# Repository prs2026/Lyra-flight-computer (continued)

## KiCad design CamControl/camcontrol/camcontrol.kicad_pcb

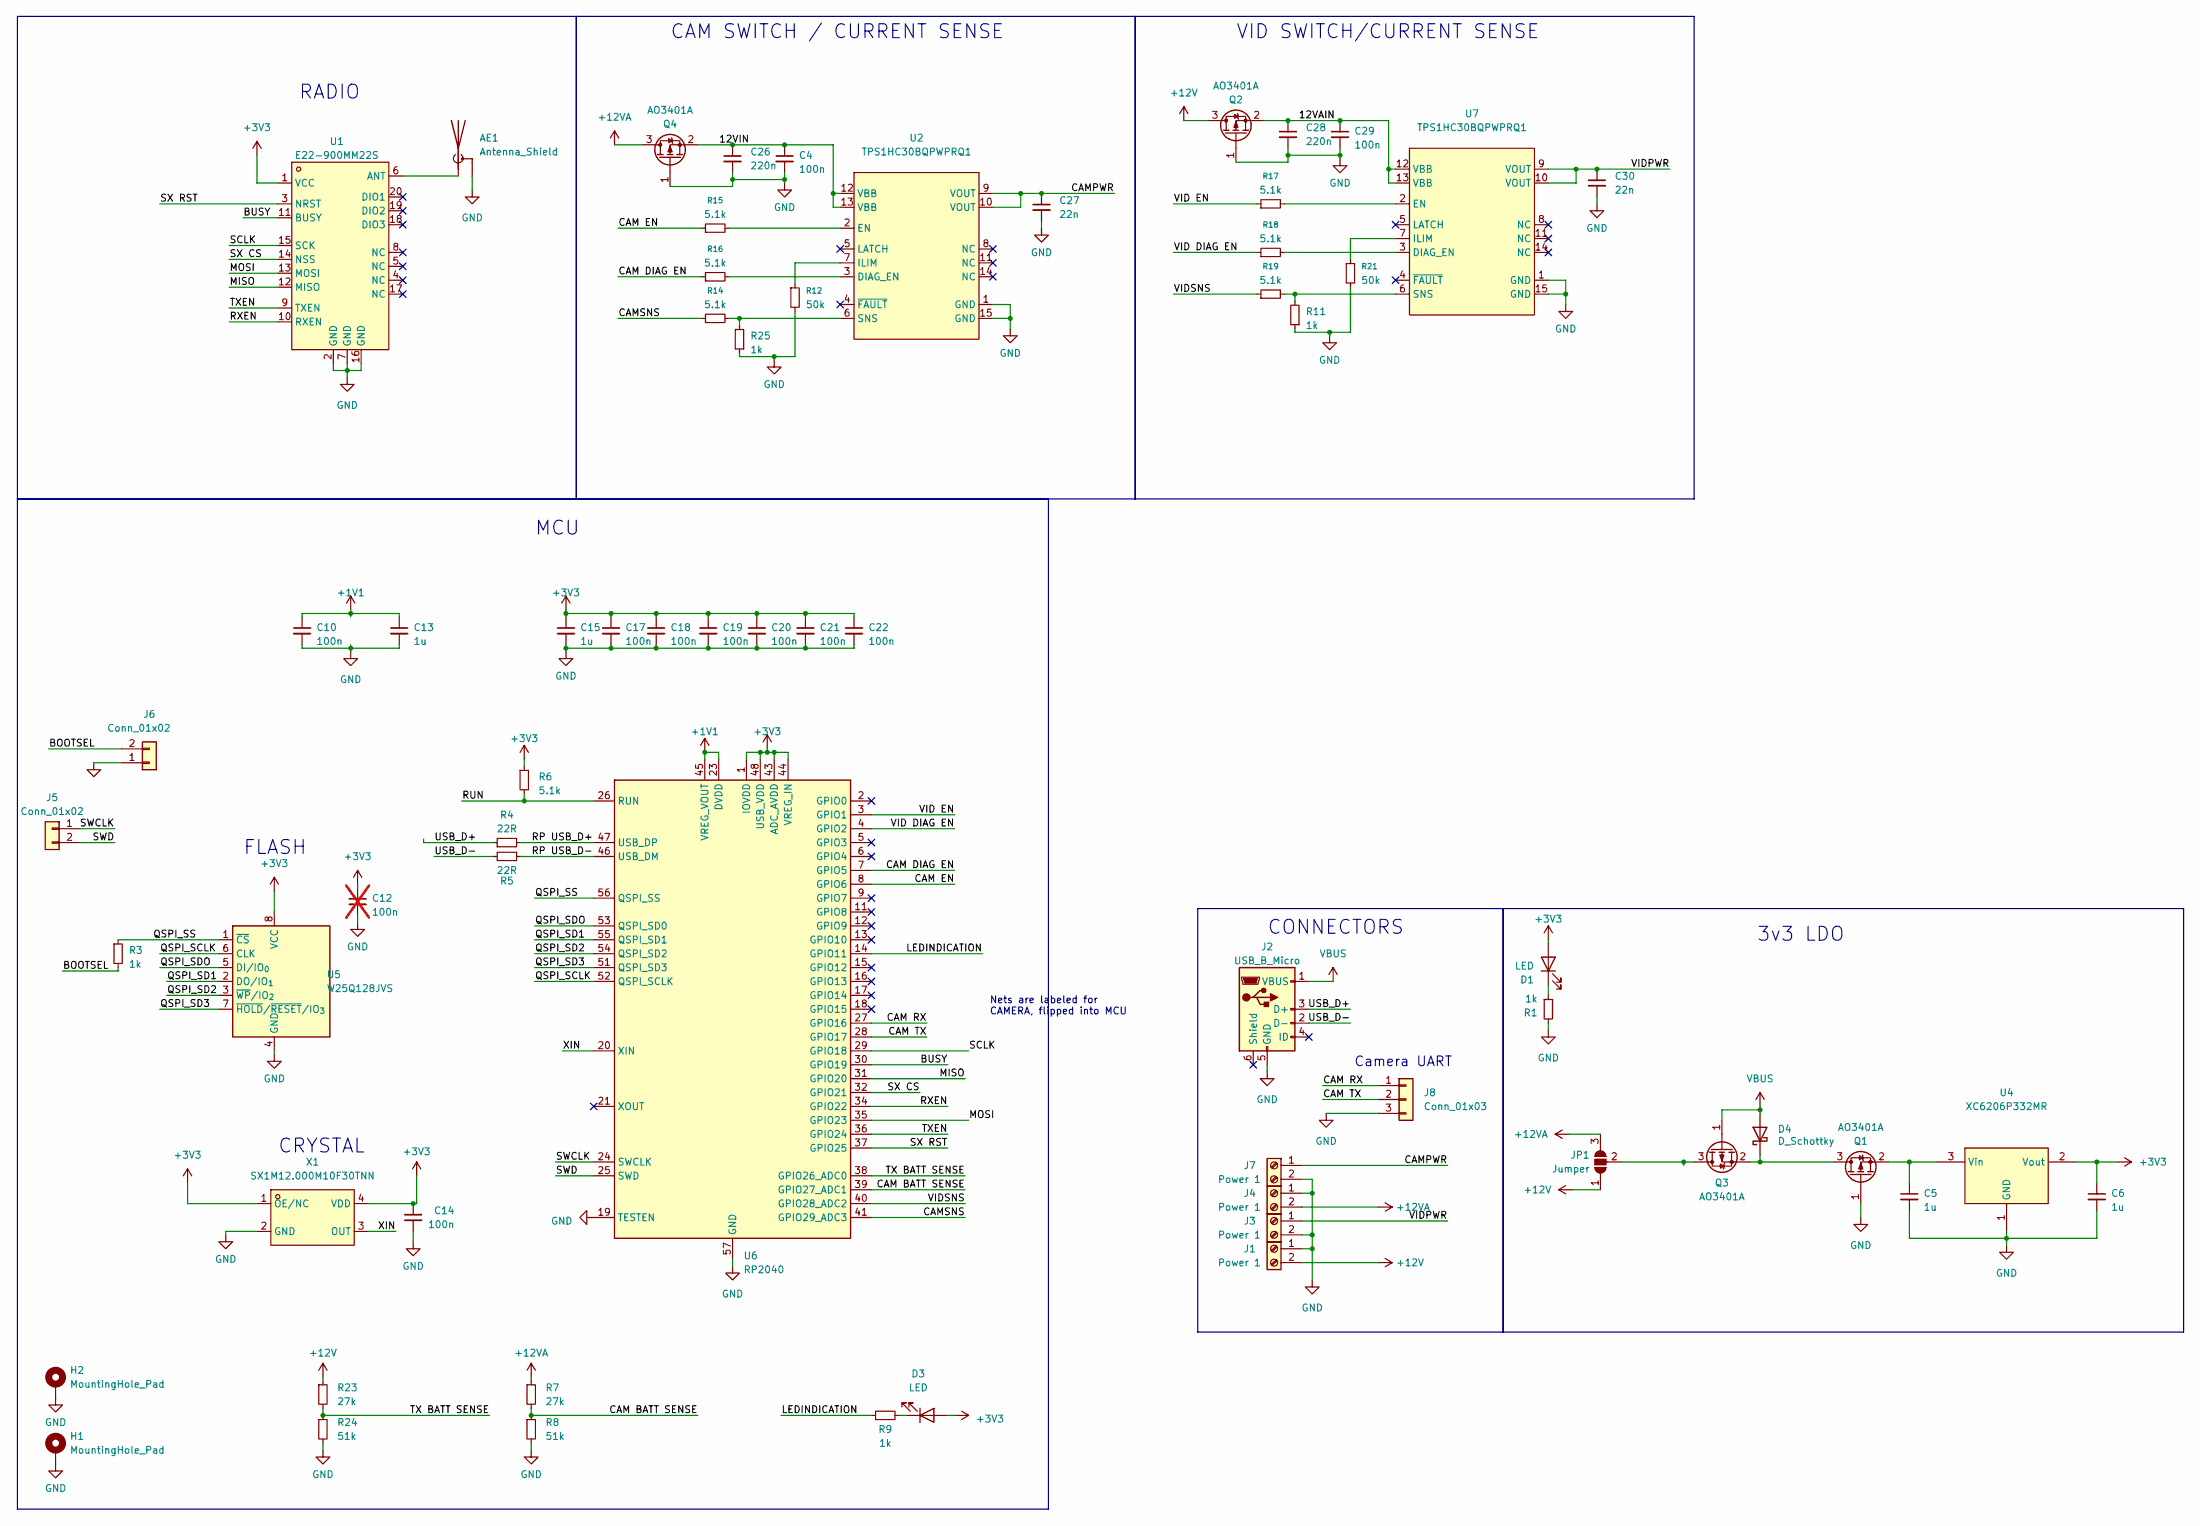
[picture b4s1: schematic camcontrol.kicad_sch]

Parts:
AE1: Antenna_Shield; ANT-SMD_1909763-1; LCSC Part C392444
C4, C10, C14, C17, C18, C19, C20, C21, C22, C29: 100n; C_0402_1005Metric; LCSC Part C1525
C5, C6, C13, C15: 1u; C_0402_1005Metric; LCSC Part C52923
C12: 100n; C_0402_1005Metric; LCSC Part C1525; not fitted
C26, C28: 220n; C_0402_1005Metric; LCSC Part C16772
C27, C30: 22n; C_0402_1005Metric; LCSC Part C1532
D1, D3: LED; LED_0603_1608Metric; LCSC Part C89811
D4: D_Schottky; D_SOD-323F; LCSC Part C191023
H1, H2: MountingHole_Pad; MountingHole_2.2mm_M2_DIN965_Pad
J1, J3, J4, J7: Power 1; wago2pin3mmspace
J2: USB_B_Micro; MICRO-USB-SMD_U254-051T-4BHJ25-F2S; LCSC Part C381143
J5: Conn_01x02; SolderJumper-2_P1.3mm_Open_Pad1.0x1.5mm
J6: Conn_01x02; SolderJumper-2_P1.3mm_Open_RoundedPad1.0x1.5mm
J8: Conn_01x03; PinHeader_1x03_P2.00mm_Vertical
JP1: Jumper; SolderJumper-3_P1.3mm_Open_RoundedPad1.0x1.5mm
Q1, Q2, Q3, Q4: AO3401A; SOT-23; LCSC Part C15127
R1, R3, R9, R11, R25: 1k; R_0402_1005Metric; LCSC Part C11702
R4, R5: 22R; R_0402_1005Metric; LCSC Part C25092
R6, R14, R15, R16, R17, R18, R19: 5.1k; R_0402_1005Metric; LCSC Part C25905
R7, R23: 27k; R_0402_1005Metric; LCSC Part C25771
R8, R24: 51k; R_0402_1005Metric; LCSC Part C25794
R12, R21: 50k; R_0402_1005Metric; LCSC Part C25897
U1: E22-900MM22S; WIRELM-SMD_E22-400MM22S; LCSC Part C5333984
U2, U7: TPS1HC30BQPWPRQ1; HTSSOP-14_L5.0-W4.4-P0.65-LS6.4-BL-EP-3; LCSC Part C7496534
U4: XC6206P332MR; SOT-23-3; LCSC Part C5446
U5: W25Q128JVS; SOIC-8_5.3x5.3mm_P1.27mm; LCSC Part C97521
U6: RP2040; QFN-56-1EP_7x7mm_P0.4mm_EP3.2x3.2mm; LCSC Part C2040
X1: SX1M12.000M10F30TNN; OSC-SMD_4P-L2.0-W1.6-BL; LCSC Part C2901608

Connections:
+1V1: C10.1, C13.1, U6.23 (DVDD), U6.45 (VREG_VOUT), U6.50 (DVDD)
+3V3: C6.1, C12.1, C14.1, C15.1, C17.1, C18.1, C19.1, C20.1, C21.1, C22.1, D1.2 (A), D3.2 (A), R6.1, U1.1 (VCC), U4.2 (Vout), U5.8 (VCC), U6.1 (IOVDD), U6.10 (IOVDD), U6.22 (IOVDD), U6.33 (IOVDD), U6.42 (IOVDD), U6.43 (ADC_AVDD), U6.44 (VREG_IN), U6.48 (USB_VDD), U6.49 (IOVDD), X1.1 (OE/NC), X1.4 (VDD)
+12V: J1.2, JP1.1 (A), Q2.3 (D), R23.1
+12VA: J4.2, JP1.3 (B), Q4.3 (D), R7.1
/12VAIN: C28.1, C29.1, Q2.2 (S), U7.12 (VBB), U7.13 (VBB)
/12VIN: C4.1, C26.1, Q4.2 (S), U2.12 (VBB), U2.13 (VBB)
/BOOTSEL: J6.2, R3.2
/BUSY: U1.11 (BUSY), U6.30 (GPIO19)
/CAM BATT SENSE: R7.2, R8.1, U6.39 (GPIO27_ADC1)
/CAM DIAG EN: R16.1, U6.7 (GPIO5)
/CAM EN: R15.1, U6.8 (GPIO6)
/CAM RX: J8.1, U6.27 (GPIO16)
/CAM TX: J8.2, U6.28 (GPIO17)
/CAMPWR: C27.1, J7.1, U2.9 (VOUT), U2.10 (VOUT)
/CAMSNS: R14.1, U6.41 (GPIO29_ADC3)
/LEDINDICATION: R9.1, U6.14 (GPIO11)
/MISO: U1.12 (MISO), U6.31 (GPIO20)
/MOSI: U1.13 (MOSI), U6.35 (GPIO23)
/QSPI_SCLK: U5.6 (CLK), U6.52 (QSPI_SCLK)
/QSPI_SD1: U5.2 (DO/IO_{1}), U6.55 (QSPI_SD1)
/QSPI_SD2: U5.3 (~WP/IO_{2}), U6.54 (QSPI_SD2)
/QSPI_SD3: U5.7 (~HOLD/~RESET/IO_{3}), U6.51 (QSPI_SD3)
/QSPI_SDO: U5.5 (DI/IO_{0}), U6.53 (QSPI_SD0)
/QSPI_SS: R3.1, U5.1 (~CS), U6.56 (QSPI_SS)
/RP USB_D+: R4.2, U6.47 (USB_DP)
/RP USB_D-: R5.1, U6.46 (USB_DM)
/RUN: R6.2, U6.26 (RUN)
/RXEN: U1.10 (RXEN), U6.34 (GPIO22)
/SCLK: U1.15 (SCK), U6.29 (GPIO18)
/SWCLK: J5.1, U6.24 (SWCLK)
/SWD: J5.2, U6.25 (SWD)
/SX CS: U1.14 (NSS), U6.32 (GPIO21)
/SX RST: U1.3 (NRST), U6.37 (GPIO25)
/TX BATT SENSE: R23.2, R24.1, U6.38 (GPIO26_ADC0)
/TXEN: U1.9 (TXEN), U6.36 (GPIO24)
/USB_D+: J2.3 (D+), R4.1
/USB_D-: J2.2 (D-), R5.2
/VID DIAG EN: R18.1, U6.4 (GPIO2)
/VID EN: R17.1, U6.3 (GPIO1)
/VIDPWR: C30.1, J3.1, U7.9 (VOUT), U7.10 (VOUT)
/VIDSNS: R19.1, U6.40 (GPIO28_ADC2)
/XIN: U6.20 (XIN), X1.3 (OUT)
GND: AE1.2 (Shield), C4.2, C5.2, C6.2, C10.2, C12.2, C13.2, C14.2, C15.2, C17.2, C18.2, C19.2, C20.2, C21.2, C22.2, C26.2, C27.2, C28.2, C29.2, C30.2, H1.1, H2.1, J1.1, J2.5 (GND), J3.2, J4.1, J6.1, J7.2, J8.3, Q1.1 (G), Q2.1 (G), Q4.1 (G), R1.2, R8.2, R11.1, R12.2, R21.2, R24.2, R25.1, U1.2 (GND), U1.7 (GND), U1.16 (GND), U2.1 (GND), U2.15 (GND), U4.1 (GND), U5.4 (GND), U6.19 (TESTEN), U6.57 (GND), U7.1 (GND), U7.15 (GND), X1.2 (GND)
unnamed: AE1.1 (A), U1.6 (ANT)
unnamed: D1.1 (K), R1.1
unnamed: D3.1 (K), R9.2
unnamed: D4.1 (K), Q1.3 (D), Q3.2 (S)
unnamed: JP1.2 (C), Q3.3 (D)
unnamed: C5.1, Q1.2 (S), U4.3 (Vin)
unnamed: R16.2, U2.3 (DIAG_EN)
unnamed: R15.2, U2.2 (EN)
unnamed: R12.1, U2.7 (ILIM)
unnamed: R14.2, R25.2, U2.6 (SNS)
unnamed: R18.2, U7.3 (DIAG_EN)
unnamed: R17.2, U7.2 (EN)
unnamed: R21.1, U7.7 (ILIM)
unnamed: R11.2, R19.2, U7.6 (SNS)
VBUS: D4.2 (A), J2.1 (VBUS), Q3.1 (G)

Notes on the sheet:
CONNECTORS
RADIO
FLASH
Camera UART
MCU
Nets are labeled for CAMERA, flipped into MCU
VID SWITCH/CURRENT SENSE
CAM SWITCH / CURRENT SENSE
3v3 LDO
CRYSTAL

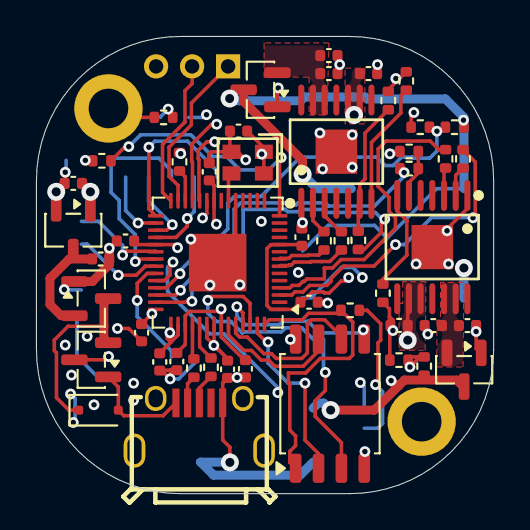
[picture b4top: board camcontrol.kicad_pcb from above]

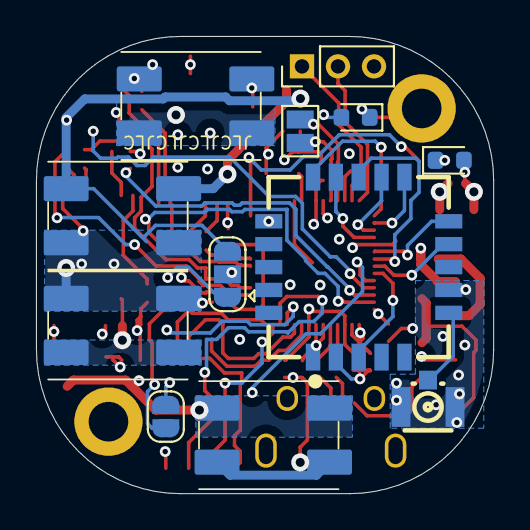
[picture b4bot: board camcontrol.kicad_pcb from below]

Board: 4 copper layers, 25.4 x 25.4 mm, 64 parts (12 on the bottom side), 58 nets.

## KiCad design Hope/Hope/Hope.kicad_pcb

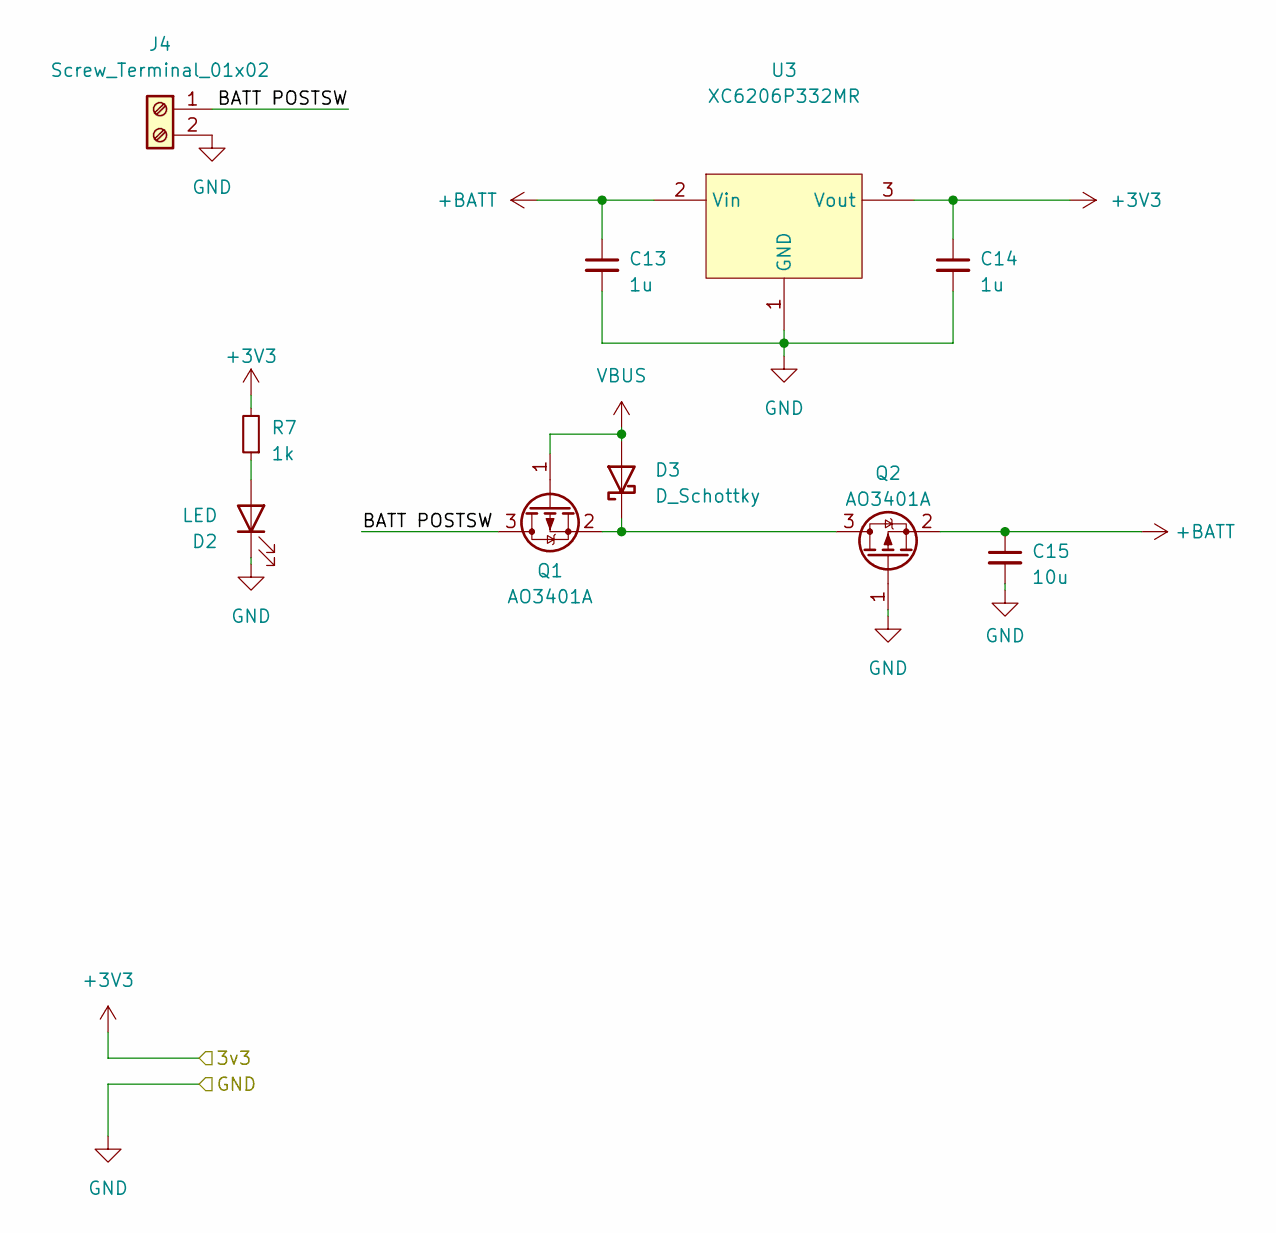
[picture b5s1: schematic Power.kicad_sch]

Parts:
C13, C14: 1u; C_0402_1005Metric; LCSC Part C52923
C15: 10u; C_0603_1608Metric; LCSC Part C96446
D2: LED; LED_0805_2012Metric
D3: D_Schottky; D_SOD-323F; LCSC Part C191023
J4: Screw_Terminal_01x02; TerminalBlock_Phoenix_MPT-0,5-2-2.54_1x02_P2.54mm_Horizontal
Q1, Q2: AO3401A; SOT-23; LCSC Part C15127
R7: 1k; R_0402_1005Metric; LCSC Part C11702
U3: XC6206P332MR; SOT-23-3_L2.9-W1.6-P1.90-LS2.8-BR; LCSC Part C5446

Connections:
+3V3: C14.1, R7.2, U3.3 (Vout); also elsewhere on the board
+BATT: C13.1, C15.1, Q2.2 (S), U3.2 (Vin); also elsewhere on the board
/Power/BATT POSTSW: J4.1, Q1.3 (D)
GND: C13.2, C14.2, C15.2, D2.1 (K), J4.2, Q2.1 (G), U3.1 (GND); also elsewhere on the board
unnamed: D2.2 (A), R7.1
unnamed: D3.1 (K), Q1.2 (S), Q2.3 (D)
VBUS: D3.2 (A), Q1.1 (G); also elsewhere on the board

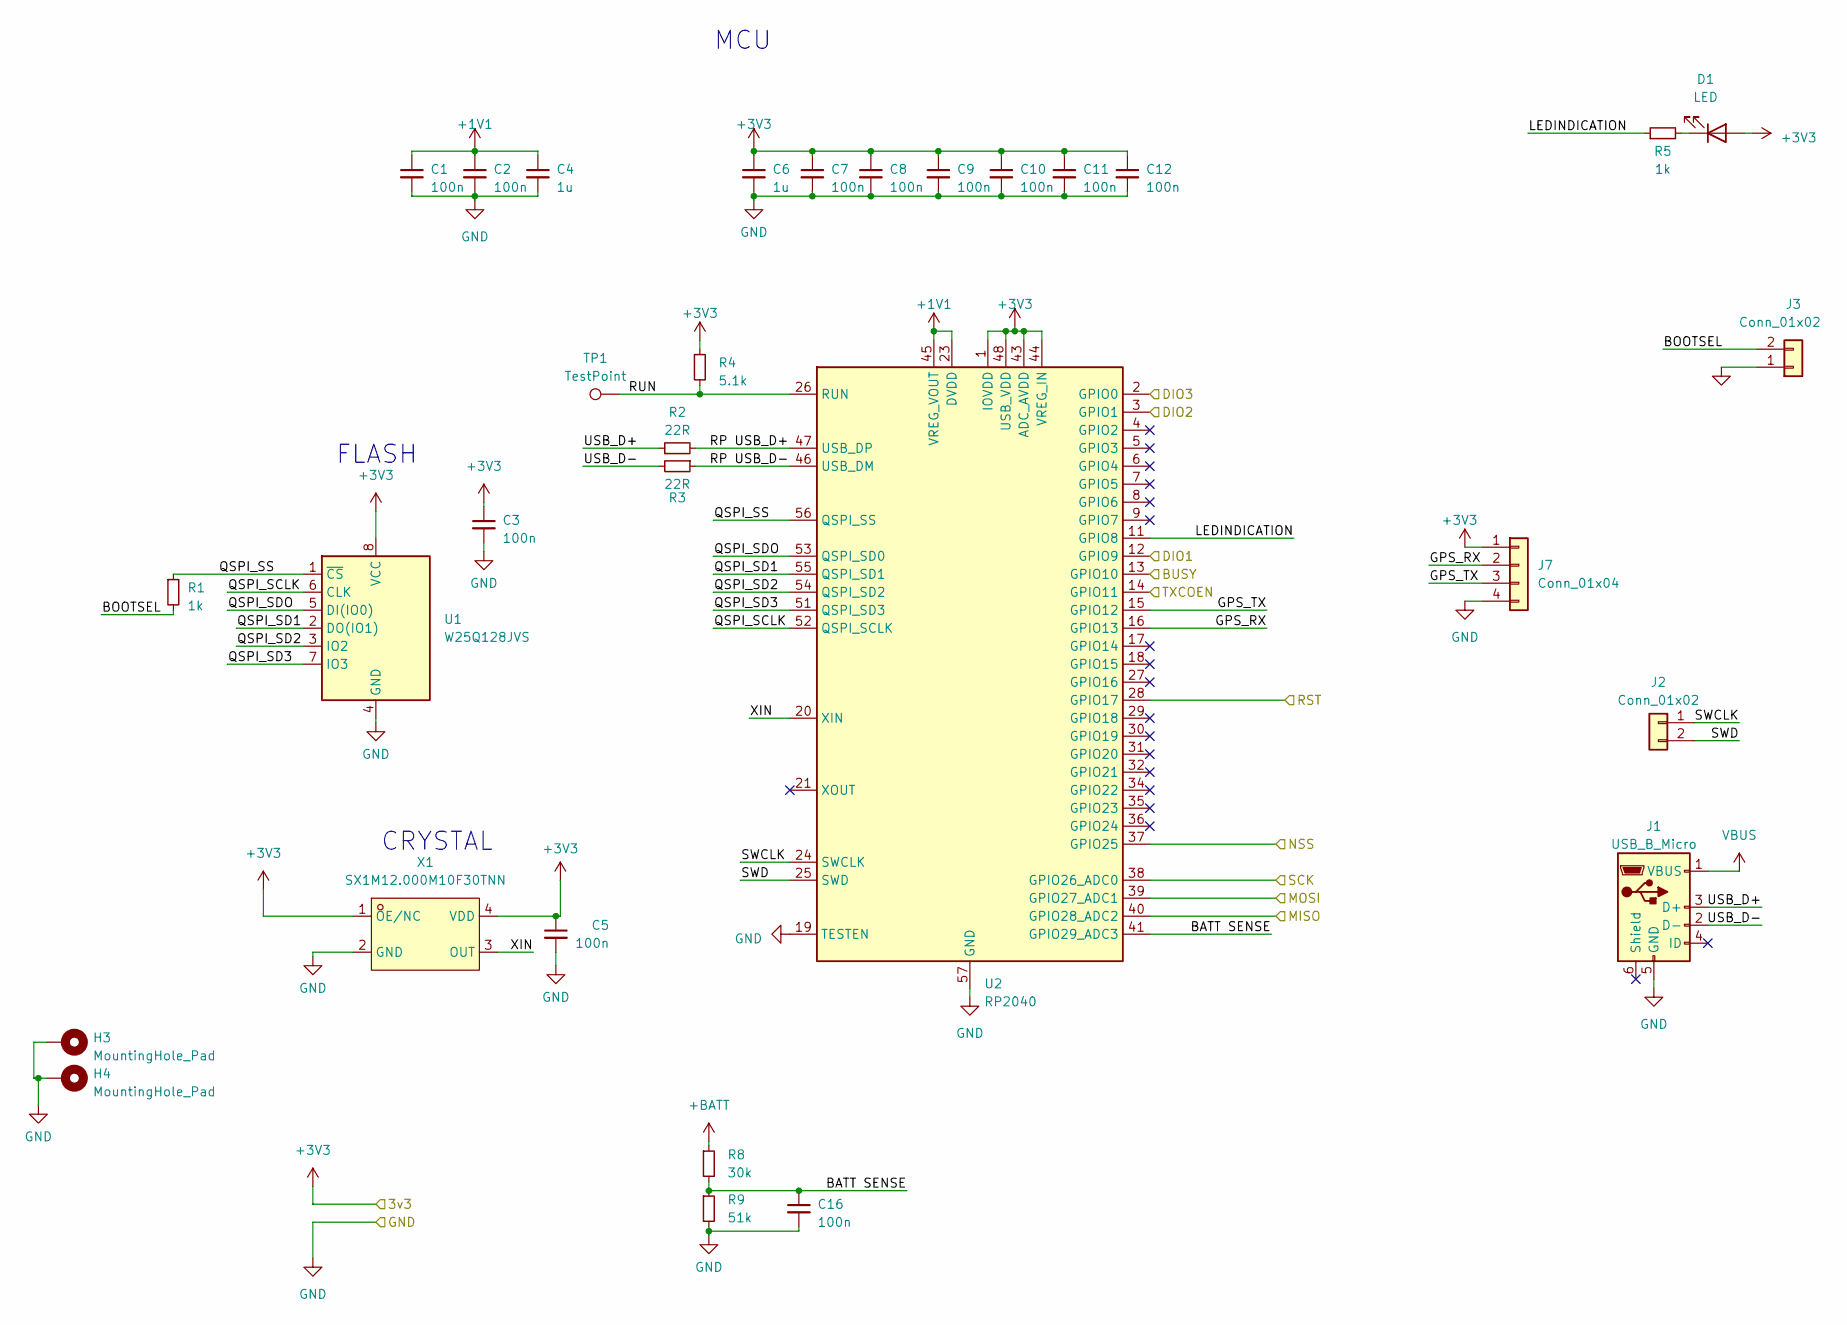
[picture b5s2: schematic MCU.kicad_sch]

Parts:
C1, C2, C3, C5, C7, C8, C9, C10, C11, C12, C16: 100n; C_0402_1005Metric; LCSC Part C1525
C4, C6: 1u; C_0402_1005Metric; LCSC Part C52923
D1: LED; LED_0805_2012Metric
H3, H4: MountingHole_Pad; MountingHole_2.2mm_M2_DIN965_Pad
J1: USB_B_Micro; MICRO-USB-SMD_U254-051T-4BHJ25-F2S; LCSC Part C381143
J2: Conn_01x02; SolderJumper-2_P1.3mm_Open_Pad1.0x1.5mm
J3: Conn_01x02; SolderJumper-2_P1.3mm_Open_RoundedPad1.0x1.5mm
J7: Conn_01x04; 4 pads 2.54mm spacign; LCSC Part C160404
R1, R5: 1k; R_0402_1005Metric; LCSC Part C11702
R2, R3: 22R; R_0402_1005Metric; LCSC Part C25092
R4: 5.1k; R_0402_1005Metric; LCSC Part C25905
R8: 30k; R_0402_1005Metric; LCSC Part C25105
R9: 51k; R_0402_1005Metric; LCSC Part C25794
TP1: TestPoint; TestPoint_Pad_1.0x1.0mm
U1: W25Q128JVS; SOIC-8_5.23x5.23mm_P1.27mm; LCSC Part C97521
U2: RP2040; QFN-56-1EP_7x7mm_P0.4mm_EP3.2x3.2mm; LCSC Part C2040
X1: SX1M12.000M10F30TNN; OSC-SMD_4P-L2.0-W1.6-BL; LCSC Part C2901608

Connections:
+1V1: C1.1, C2.1, C4.1, U2.23 (DVDD), U2.45 (VREG_VOUT), U2.50 (DVDD)
+3V3: C3.1, C5.1, C6.1, C7.1, C8.1, C9.1, C10.1, C11.1, C12.1, D1.2 (A), J7.1, R4.1, U1.8 (VCC), U2.1 (IOVDD), U2.10 (IOVDD), U2.22 (IOVDD), U2.33 (IOVDD), U2.42 (IOVDD), U2.43 (ADC_AVDD), U2.44 (VREG_IN), U2.48 (USB_VDD), U2.49 (IOVDD), X1.1 (OE/NC), X1.4 (VDD); also elsewhere on the board
+BATT: R8.1; also elsewhere on the board
/MCU/BATT SENSE: C16.1, R8.2, R9.1, U2.41 (GPIO29_ADC3)
/MCU/BOOTSEL: J3.2, R1.2
/MCU/BUSY: U2.13 (GPIO10); also elsewhere on the board
/MCU/DIO1: U2.12 (GPIO9); also elsewhere on the board
/MCU/DIO2: U2.3 (GPIO1); also elsewhere on the board
/MCU/DIO3: U2.2 (GPIO0); also elsewhere on the board
/MCU/GPS_RX: J7.2, U2.16 (GPIO13)
/MCU/GPS_TX: J7.3, U2.15 (GPIO12)
/MCU/LEDINDICATION: R5.1, U2.11 (GPIO8)
/MCU/MISO: U2.40 (GPIO28_ADC2); also elsewhere on the board
/MCU/MOSI: U2.39 (GPIO27_ADC1); also elsewhere on the board
/MCU/NSS: U2.37 (GPIO25); also elsewhere on the board
/MCU/QSPI_SCLK: U1.6 (CLK), U2.52 (QSPI_SCLK)
/MCU/QSPI_SD1: U1.2 (DO(IO1)), U2.55 (QSPI_SD1)
/MCU/QSPI_SD2: U1.3 (IO2), U2.54 (QSPI_SD2)
/MCU/QSPI_SD3: U1.7 (IO3), U2.51 (QSPI_SD3)
/MCU/QSPI_SDO: U1.5 (DI(IO0)), U2.53 (QSPI_SD0)
/MCU/QSPI_SS: R1.1, U1.1 (~CS), U2.56 (QSPI_SS)
/MCU/RP USB_D+: R2.2, U2.47 (USB_DP)
/MCU/RP USB_D-: R3.1, U2.46 (USB_DM)
/MCU/RST: U2.28 (GPIO17)
/MCU/RUN: R4.2, TP1.1, U2.26 (RUN)
/MCU/SCK: U2.38 (GPIO26_ADC0); also elsewhere on the board
/MCU/SWCLK: J2.1, U2.24 (SWCLK)
/MCU/SWD: J2.2, U2.25 (SWD)
/MCU/TXCOEN: U2.14 (GPIO11); also elsewhere on the board
/MCU/USB_D+: J1.3 (D+), R2.1
/MCU/USB_D-: J1.2 (D-), R3.2
/MCU/XIN: U2.20 (XIN), X1.3 (OUT)
GND: C1.2, C2.2, C3.2, C4.2, C5.2, C6.2, C7.2, C8.2, C9.2, C10.2, C11.2, C12.2, C16.2, H3.1, H4.1, J1.5 (GND), J3.1, J7.4, R9.2, U1.4 (GND), U2.19 (TESTEN), U2.57 (GND), X1.2 (GND); also elsewhere on the board
unnamed: D1.1 (K), R5.2
VBUS: J1.1 (VBUS); also elsewhere on the board

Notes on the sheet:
FLASH
MCU
CRYSTAL

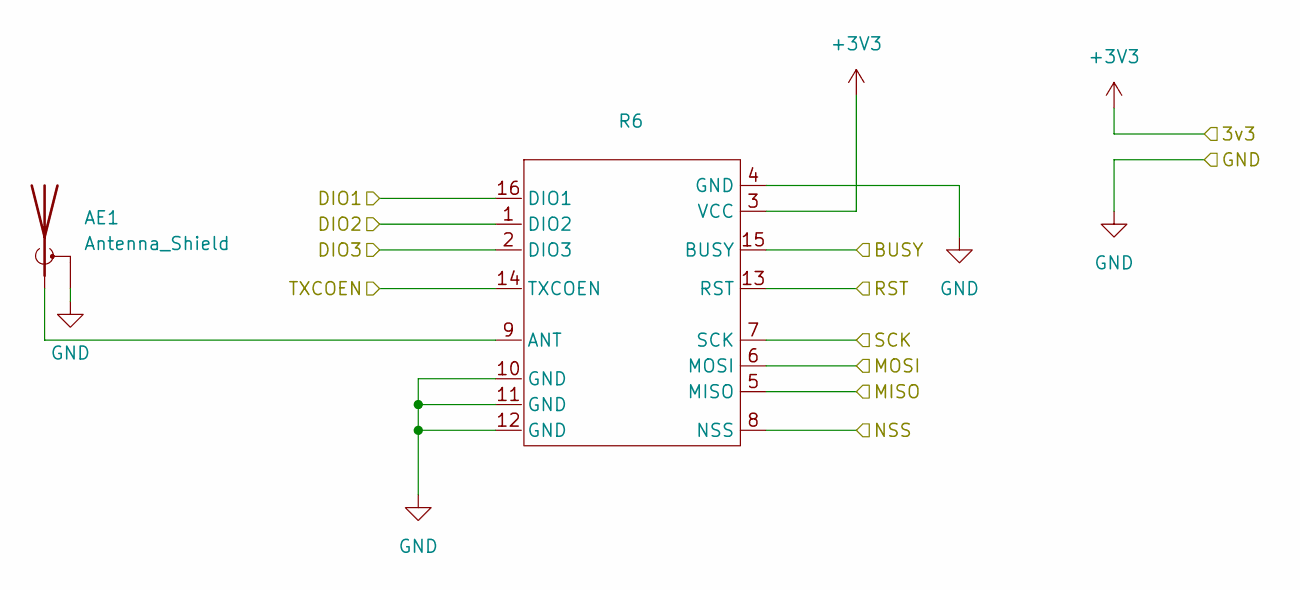
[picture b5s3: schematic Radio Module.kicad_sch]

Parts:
AE1: Antenna_Shield; CONN-SMD_KH-SMA-KE8-G; LCSC Part C530661
R6: WIRELM-SMD_16P-L16.0-W16.0-P2.00_LORA1280-TCXO

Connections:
+3V3: R6.3 (VCC); also elsewhere on the board
/MCU/BUSY: R6.15 (BUSY); also elsewhere on the board
/MCU/DIO1: R6.16 (DIO1); also elsewhere on the board
/MCU/DIO2: R6.1 (DIO2); also elsewhere on the board
/MCU/DIO3: R6.2 (DIO3); also elsewhere on the board
/MCU/MISO: R6.5 (MISO); also elsewhere on the board
/MCU/MOSI: R6.6 (MOSI); also elsewhere on the board
/MCU/NSS: R6.8 (NSS); also elsewhere on the board
/MCU/SCK: R6.7 (SCK); also elsewhere on the board
/MCU/TXCOEN: R6.14 (TXCOEN); also elsewhere on the board
/Radio Module/RST: R6.13 (RST)
GND: AE1.2 (Shield), R6.4 (GND), R6.10 (GND), R6.11 (GND), R6.12 (GND); also elsewhere on the board
unnamed: AE1.1 (A), R6.9 (ANT)

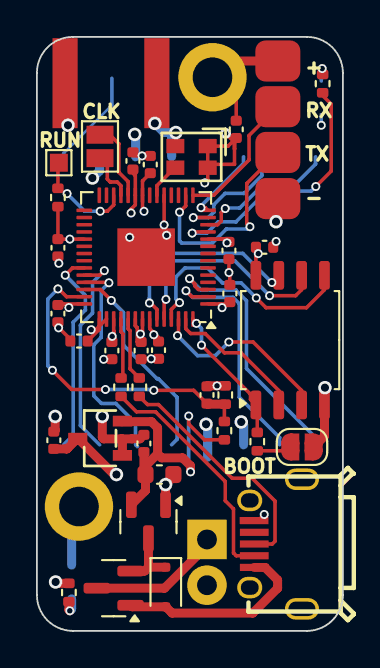
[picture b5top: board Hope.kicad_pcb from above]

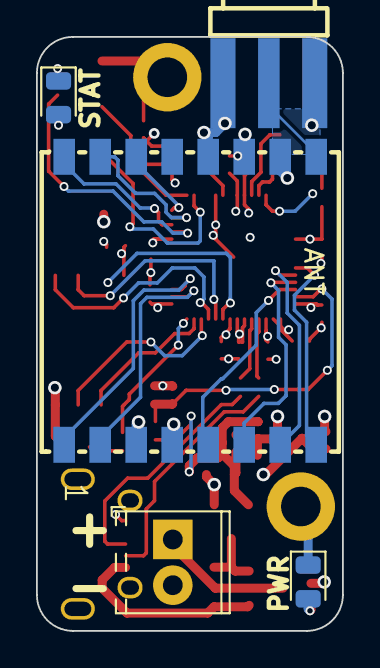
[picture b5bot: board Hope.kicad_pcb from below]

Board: 4 copper layers, 17.0 x 33.0 mm, 43 parts (5 on the bottom side), 38 nets.

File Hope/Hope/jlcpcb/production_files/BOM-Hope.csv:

Comment,Designator,Footprint,LCSC
1k,"R1,R5,R7",R_0402_1005Metric,C11702
AO3401A,"Q1,Q2",SOT-23,C15127
100n,"C1,C10,C11,C12,C16,C2,C3,C5,C7,C8,C9",C_0402_1005Metric,C1525
D_Schottky,D3,D_SOD-323F,C191023
RP2040,U2,QFN-56-1EP_7x7mm_P0.4mm_EP3.2x3.2mm,C2040
22R,"R2,R3",R_0402_1005Metric,C25092
30k,R8,R_0402_1005Metric,C25105
51k,R9,R_0402_1005Metric,C25794
5.1k,R4,R_0402_1005Metric,C25905
SX1M12.000M10F30TNN,X1,OSC-SMD_4P-L2.0-W1.6-BL,C2901608
USB_B_Micro,J1,MICRO-USB-SMD_U254-051T-4BHJ25-F2S,C381143
1u,"C13,C14,C4,C6",C_0402_1005Metric,C52923
Antenna_Shield,AE1,CONN-SMD_KH-SMA-KE8-G,C530661
XC6206P332MR,U3,SOT-23-3_L2.9-W1.6-P1.90-LS2.8-BR,C5446
10u,C15,C_0603_1608Metric,C96446
W25Q128JVS,U1,SOIC-8_5.23x5.23mm_P1.27mm,C97521

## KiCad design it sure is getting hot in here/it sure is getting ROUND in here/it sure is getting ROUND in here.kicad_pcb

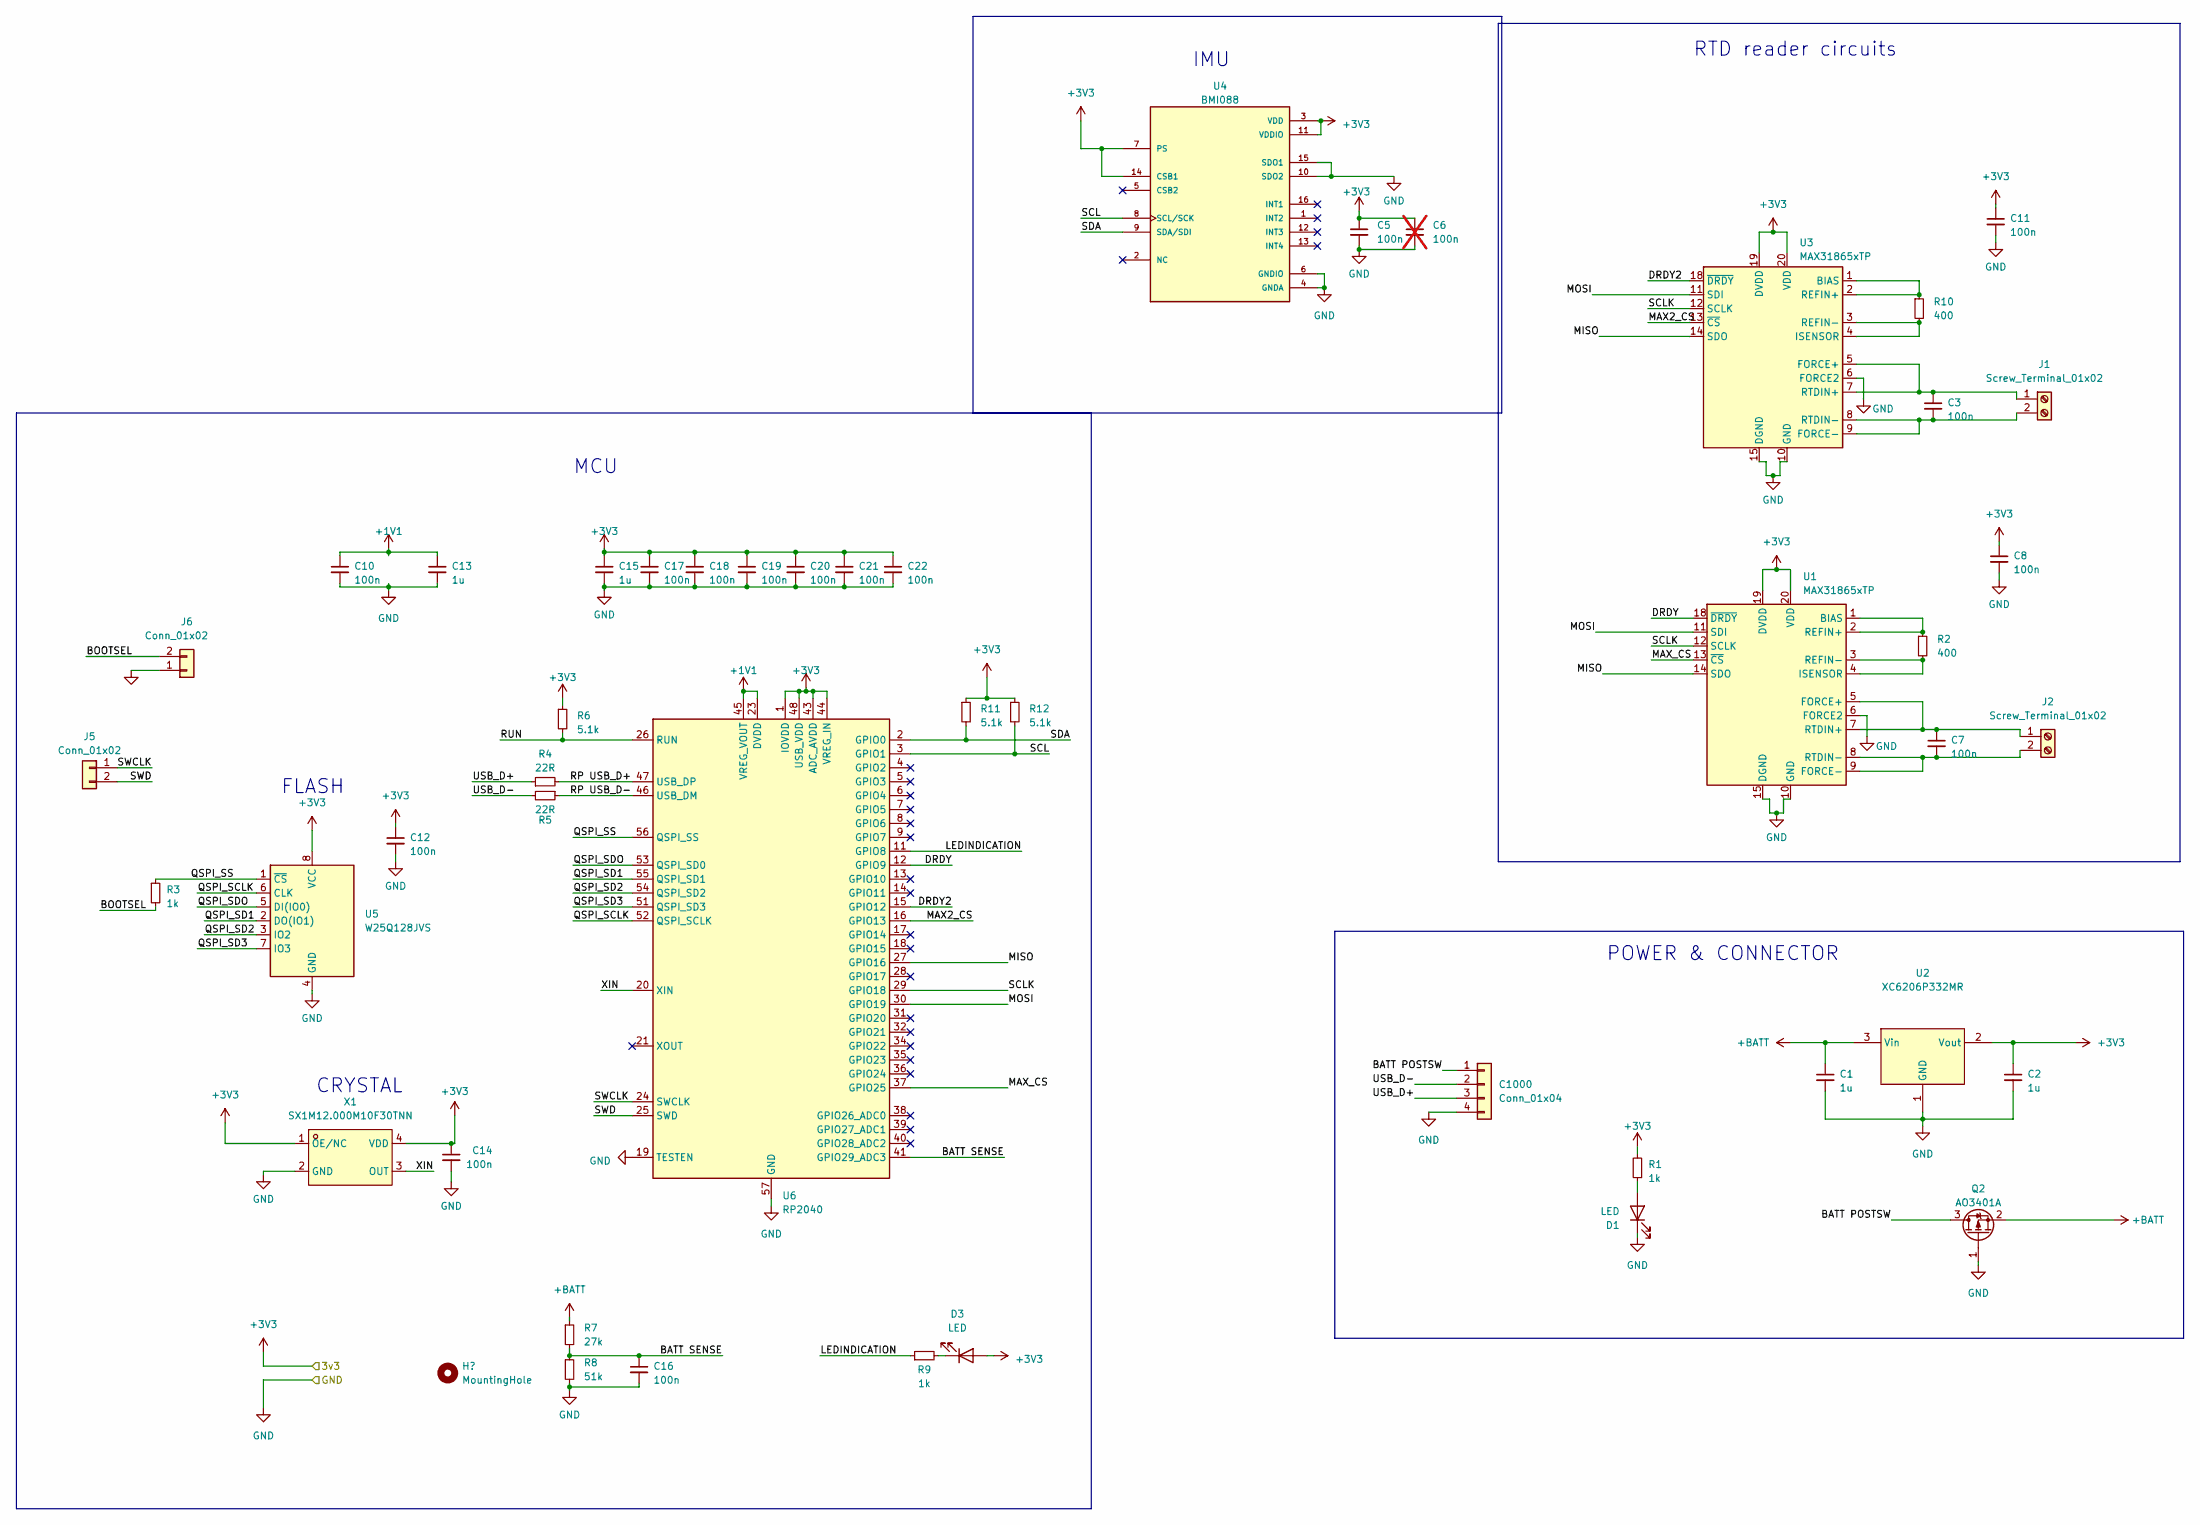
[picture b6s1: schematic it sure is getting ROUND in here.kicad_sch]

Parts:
C1, C2, C13, C15: 1u; C_0402_1005Metric; LCSC Part C52923
C3, C7, C8, C10, C11, C12, C14, C16, C17, C18, C19, C20, C21, C22: 100n; C_0402_1005Metric; LCSC Part C1525
C5: 100n; C_0603_1608Metric_Pad1.08x0.95mm_HandSolder; LCSC Part C1525
C6: 100n; C_0603_1608Metric_Pad1.08x0.95mm_HandSolder; LCSC Part C1525; not fitted
C1000: Conn_01x04; CONN-SMD_1.25-4PWB; LCSC Part C2905011
D1, D3: LED; LED_0603_1608Metric; LCSC Part C89811
J1, J2: Screw_Terminal_01x02; SolderJumper-2_P1.3mm_Open_Pad1.0x1.5mm
J5: Conn_01x02; SolderJumper-2_P1.3mm_Open_Pad1.0x1.5mm
J6: Conn_01x02; SolderJumper-2_P1.3mm_Open_RoundedPad1.0x1.5mm
Q2: AO3401A; SOT-23; LCSC Part C15127
R1, R3, R9: 1k; R_0402_1005Metric; LCSC Part C11702
R2, R10: 400; R_0402_1005Metric; LCSC Part C41042
R4, R5: 22R; R_0402_1005Metric; LCSC Part C25092
R6, R11, R12: 5.1k; R_0402_1005Metric; LCSC Part C25905
R7: 27k; R_0402_1005Metric; LCSC Part C25771
R8: 51k; R_0402_1005Metric; LCSC Part C25794
U1, U3: MAX31865xTP; TQFN-20-1EP_5x5mm_P0.65mm_EP3.25x3.25mm; LCSC Part C118474
U2: XC6206P332MR; SOT-23-3; LCSC Part C5446
U4: BMI088; LGA-16_L4.5-W3.0-P0.50-BL; LCSC Part C194919
U5: W25Q128JVS; SOIC-8_5.23x5.23mm_P1.27mm; LCSC Part C97521
U6: RP2040; QFN-56-1EP_7x7mm_P0.4mm_EP3.2x3.2mm; LCSC Part C2040
X1: SX1M12.000M10F30TNN; OSC-SMD_4P-L2.0-W1.6-BL; LCSC Part C2901608

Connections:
+1V1: C10.1, C13.1, U6.23 (DVDD), U6.45 (VREG_VOUT), U6.50 (DVDD)
+3V3: C2.1, C5.1, C6.1, C8.1, C11.1, C12.1, C14.1, C15.1, C17.1, C18.1, C19.1, C20.1, C21.1, C22.1, D3.2 (A), R1.2, R6.1, R11.1, R12.1, U1.19 (DVDD), U1.20 (VDD), U2.2 (Vout), U3.19 (DVDD), U3.20 (VDD), U4.3 (VDD), U4.7 (PS), U4.11 (VDDIO), U4.14 (CSB1), U5.8 (VCC), U6.1 (IOVDD), U6.10 (IOVDD), U6.22 (IOVDD), U6.33 (IOVDD), U6.42 (IOVDD), U6.43 (ADC_AVDD), U6.44 (VREG_IN), U6.48 (USB_VDD), U6.49 (IOVDD), X1.1 (OE/NC), X1.4 (VDD)
+BATT: C1.1, Q2.2 (S), R7.1, U2.3 (Vin)
/BATT POSTSW: C1000.1, Q2.3 (D)
/BATT SENSE: C16.1, R7.2, R8.1, U6.41 (GPIO29_ADC3)
/BOOTSEL: J6.2, R3.2
/DRDY: U1.18 (~DRDY), U6.12 (GPIO9)
/DRDY2: U3.18 (~DRDY), U6.15 (GPIO12)
/LEDINDICATION: R9.1, U6.11 (GPIO8)
/MAX2_CS: U3.13 (~CS), U6.16 (GPIO13)
/MAX_CS: U1.13 (~CS), U6.37 (GPIO25)
/MISO: U1.14 (SDO), U3.14 (SDO), U6.27 (GPIO16)
/MOSI: U1.11 (SDI), U3.11 (SDI), U6.30 (GPIO19)
/QSPI_SCLK: U5.6 (CLK), U6.52 (QSPI_SCLK)
/QSPI_SD1: U5.2 (DO(IO1)), U6.55 (QSPI_SD1)
/QSPI_SD2: U5.3 (IO2), U6.54 (QSPI_SD2)
/QSPI_SD3: U5.7 (IO3), U6.51 (QSPI_SD3)
/QSPI_SDO: U5.5 (DI(IO0)), U6.53 (QSPI_SD0)
/QSPI_SS: R3.1, U5.1 (~CS), U6.56 (QSPI_SS)
/RP USB_D+: R4.2, U6.47 (USB_DP)
/RP USB_D-: R5.1, U6.46 (USB_DM)
/RUN: R6.2, U6.26 (RUN)
/SCL: R12.2, U4.8 (SCL/SCK), U6.3 (GPIO1)
/SCLK: U1.12 (SCLK), U3.12 (SCLK), U6.29 (GPIO18)
/SDA: R11.2, U4.9 (SDA/SDI), U6.2 (GPIO0)
/SWCLK: J5.1, U6.24 (SWCLK)
/SWD: J5.2, U6.25 (SWD)
/USB_D+: C1000.3, R4.1
/USB_D-: C1000.2, R5.2
/XIN: U6.20 (XIN), X1.3 (OUT)
GND: C1.2, C2.2, C5.2, C6.2, C8.2, C10.2, C11.2, C12.2, C13.2, C14.2, C15.2, C16.2, C17.2, C18.2, C19.2, C20.2, C21.2, C22.2, C1000.4, D1.1 (K), J6.1, Q2.1 (G), R8.2, U1.6 (FORCE2), U1.10 (GND), U1.15 (DGND), U1.16 (GND), U1.21 (GND), U2.1 (GND), U3.6 (FORCE2), U3.10 (GND), U3.15 (DGND), U3.16 (GND), U3.21 (GND), U4.4 (GNDA), U4.6 (GNDIO), U4.10 (SDO2), U4.15 (SDO1), U5.4 (GND), U6.19 (TESTEN), U6.57 (GND), X1.2 (GND)
unnamed: D1.2 (A), R1.1
unnamed: D3.1 (K), R9.2
unnamed: C3.1, J1.1, U3.5 (FORCE+), U3.7 (RTDIN+)
unnamed: C3.2, J1.2, U3.8 (RTDIN-), U3.9 (FORCE-)
unnamed: C7.1, J2.1, U1.5 (FORCE+), U1.7 (RTDIN+)
unnamed: C7.2, J2.2, U1.8 (RTDIN-), U1.9 (FORCE-)
unnamed: R2.1, U1.1 (BIAS), U1.2 (REFIN+)
unnamed: R2.2, U1.3 (REFIN-), U1.4 (ISENSOR)
unnamed: R10.1, U3.1 (BIAS), U3.2 (REFIN+)
unnamed: R10.2, U3.3 (REFIN-), U3.4 (ISENSOR)

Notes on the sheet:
CRYSTAL
POWER & CONNECTOR
RTD reader circuits
FLASH
MCU
IMU

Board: 4 copper layers, 47 parts (16 on the bottom side), 41 nets, no tracks yet.

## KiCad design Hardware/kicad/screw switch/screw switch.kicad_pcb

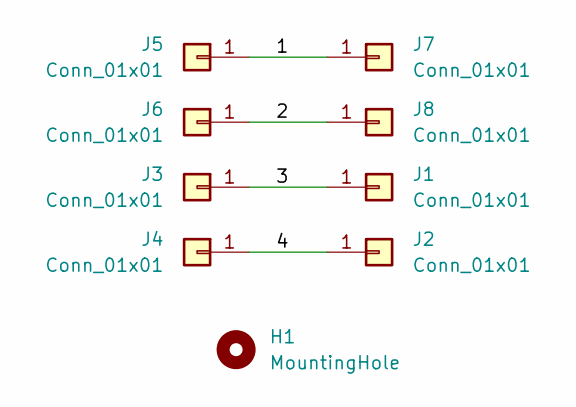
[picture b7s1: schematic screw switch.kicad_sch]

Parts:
H1: MountingHole; MountingHole_2.2mm_M2_DIN965
J1, J2, J7, J8: Conn_01x01; screwswitchpad
J3, J4, J5, J6: Conn_01x01; PinHeader_1x01_P2.54mm_Vertical

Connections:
/1: J5.1, J7.1
/2: J6.1, J8.1
/3: J1.1, J3.1
/4: J2.1, J4.1

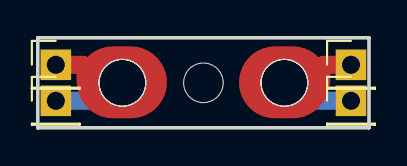
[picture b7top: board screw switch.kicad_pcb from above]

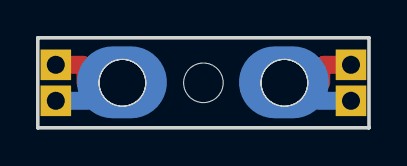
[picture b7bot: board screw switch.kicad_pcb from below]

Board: 2 copper layers, 18.4 x 5.0 mm, 9 parts (2 on the bottom side), 4 nets.
